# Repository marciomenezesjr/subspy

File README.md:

# subspy
Internet of Things final project

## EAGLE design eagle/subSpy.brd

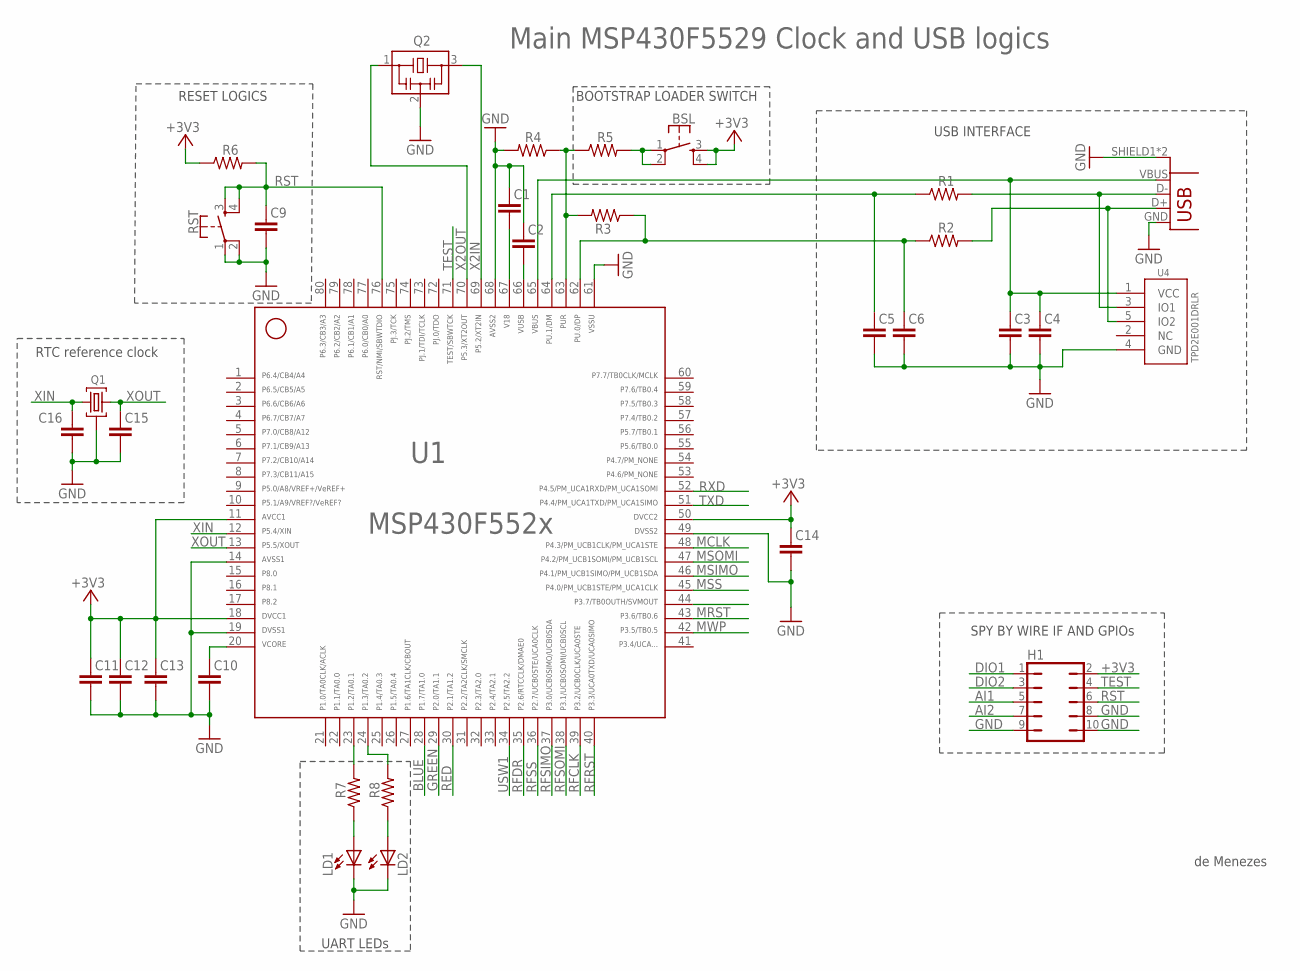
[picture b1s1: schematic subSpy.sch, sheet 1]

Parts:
BSL: DTSM-6
C1, C2: 220nF; C0402
C3: 10uF; C1206
C4, C12, C13, C14: 100nF; C0402
C5, C6: 10pF; C0603
C9: 1nF; C0603
C10: 470nF; C0603
C11: 10uF; C0805
C15, C16: 12pF; C0603
H1: JP5Q
LD1, LD2: LEDCHIP-LED0805; CHIP-LED0805
Q1: 32.768kHz; MS3V-T1R
Q2: CSTCR4M00G15L99; MURATA-FILTER_CSTCR
R1, R2: 27R; R0603
R3: 1.4k; R0603
R4: 1M; R0603
R5: 100R; R0603
R6: 47k; R0603
R7: 470R; R0603
R8: 390R; R0603
RST: DTSM-6
U1: MSP430F5529IPNR; PN80
U4: TPD2E001DRLR; TPD2E001-DRL
USB: USB_SMD; USBCONN

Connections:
+3V3: BSL.3, BSL.4, C11.1, C12.1, C13.1, C14.1, H1.2, R6.1, U1.11, U1.18, U1.50; also elsewhere on the board
AI1: H1.5
AI2: H1.7
BLUE: U1.28; also elsewhere on the board
D+: R2.2, U4.5 (IO2), USB.D+
D-: R1.2, U4.3 (IO1), USB.D-
DIO1: H1.1
DIO2: H1.3
DM: C5.1, R1.1, U1.64
DP: C6.1, R2.1, R3.1, U1.62
GND: C1.1, C2.1, C3.2, C4.2, C5.2, C6.2, C9.2, C10.2, C11.2, C12.2, C13.2, C14.2, C15.2, C16.2, H1.8, H1.9, H1.10, LD1.C, LD2.C, Q1.P3 (GND), Q2.2, R4.2, RST.1, RST.2, U1.14, U1.19, U1.49, U1.61, U1.68, U4.4 (GND), USB.GND, USB.SHIELD1 (SHIELD), USB.SHIELD2 (SHIELD); also elsewhere on the board
GREEN: U1.29; also elsewhere on the board
LD1: R7.2, U1.23
LD2: R8.2, U1.24
MCLK: U1.48; also elsewhere on the board
MRST: U1.43; also elsewhere on the board
MSIMO: U1.46; also elsewhere on the board
MSOMI: U1.47; also elsewhere on the board
MSS: U1.45; also elsewhere on the board
MWP: U1.42; also elsewhere on the board
unnamed: BSL.1, BSL.2, R5.2
unnamed: C10.1, U1.20
unnamed: LD1.A, R7.1
unnamed: LD2.A, R8.1
PUR: R3.2, R4.1, R5.1, U1.63
RED: U1.30; also elsewhere on the board
RFCLK: U1.39; also elsewhere on the board
RFDR: U1.35; also elsewhere on the board
RFRST: U1.40; also elsewhere on the board
RFSIMO: U1.37; also elsewhere on the board
RFSOMI: U1.38; also elsewhere on the board
RFSS: U1.36; also elsewhere on the board
RST: C9.1, H1.6, R6.2, RST.3, RST.4, U1.76
RXD: U1.52
TEST: H1.4, U1.71
TXD: U1.51
USW1: U1.34; also elsewhere on the board
V18: C1.2, U1.67
VBUS: C3.1, C4.1, U1.65, U4.1 (VCC), USB.VBUS; also elsewhere on the board
VUSB: C2.2, U1.66
X2IN: Q2.3, U1.69
X2OUT: Q2.1, U1.70
XIN: C16.1, Q1.P2 (2), U1.12
XOUT: C15.1, Q1.P1 (1), U1.13

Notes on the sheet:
UART LEDs
SPY BY WIRE IF AND GPIOs
USB INTERFACE
BOOTSTRAP LOADER SWITCH
RESET LOGICS
Main MSP430F5529 Clock and USB logics
RTC reference clock
de Menezes

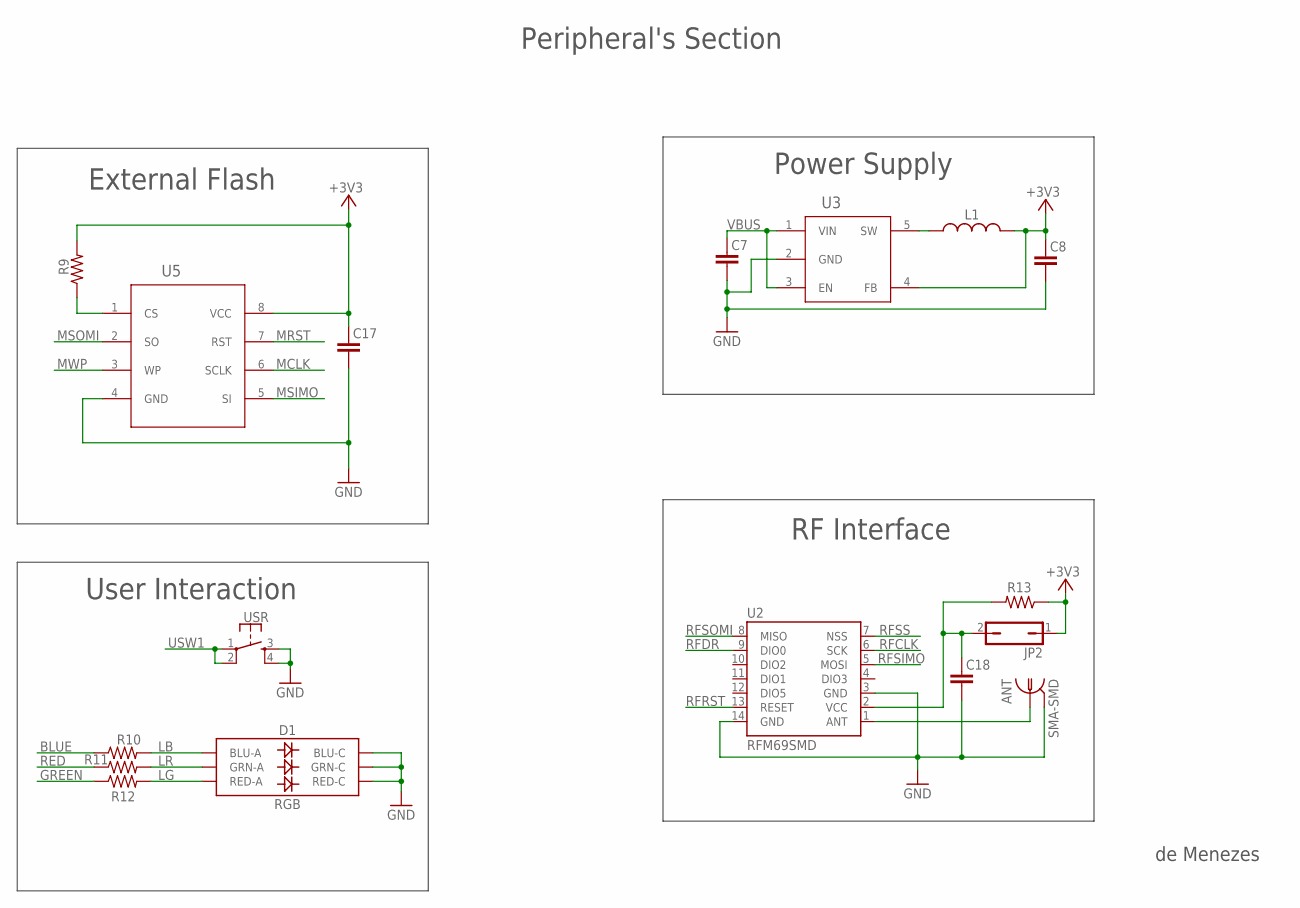
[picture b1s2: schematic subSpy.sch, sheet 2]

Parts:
ANT: SMA-SMD
C7, C8: 10uF; C0805
C17, C18: 100nF; C0402
D1: RGB; PLCC-6-LED
JP2: JP1Q; JP1
L1: INDUCTOR; L4532P
R9: 2.2k; R0603
R10, R12: ND; R0402
R11: 174R; R0402
R13: 0R; R0603
U2: RFM69SMD; RFM69
U3: Value; DBV0005A_N
U5: Value; PSA0008A_N
USR: DTSM-6

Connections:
+3V3: C8.1, C17.1, JP2.1, L1.2, R9.2, R13.1, U3.4 (FB), U5.8 (VCC); also elsewhere on the board
ANT: ANT.1, U2.1 (ANT)
BLUE: R10.1; also elsewhere on the board
GND: ANT.2@1 (2), ANT.2@2 (2), ANT.2@3 (2), ANT.2@4 (2), ANT.2@5 (2), ANT.2@6 (2), C7.2, C8.2, C17.2, C18.2, D1.CB (BLU-C), D1.CG (GRN-C), D1.CR (RED-C), U2.3 (GND), U2.14 (GND), U3.2 (GND), U5.4 (GND), USR.3, USR.4; also elsewhere on the board
GREEN: R12.1; also elsewhere on the board
LB: D1.AB (BLU-A), R10.2
LG: D1.AR (RED-A), R12.2
LR: D1.AG (GRN-A), R11.2
MCLK: U5.6 (SCLK); also elsewhere on the board
MRST: U5.7 (RST); also elsewhere on the board
MSIMO: U5.5 (SI); also elsewhere on the board
MSOMI: U5.2 (SO); also elsewhere on the board
MSS: R9.1, U5.1 (CS); also elsewhere on the board
MWP: U5.3 (WP); also elsewhere on the board
unnamed: L1.1, U3.5 (SW)
RED: R11.1; also elsewhere on the board
RFCLK: U2.6 (SCK); also elsewhere on the board
RFDR: U2.9 (DIO0); also elsewhere on the board
RFPWR: C18.1, JP2.2, R13.2, U2.2 (VCC)
RFRST: U2.13 (RESET); also elsewhere on the board
RFSIMO: U2.5 (MOSI); also elsewhere on the board
RFSOMI: U2.8 (MISO); also elsewhere on the board
RFSS: U2.7 (NSS); also elsewhere on the board
USW1: USR.1, USR.2; also elsewhere on the board
VBUS: C7.1, U3.1 (VIN), U3.3 (EN); also elsewhere on the board

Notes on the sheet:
External Flash
Power Supply
RF Interface
User Interaction
Peripheral's Section
de Menezes

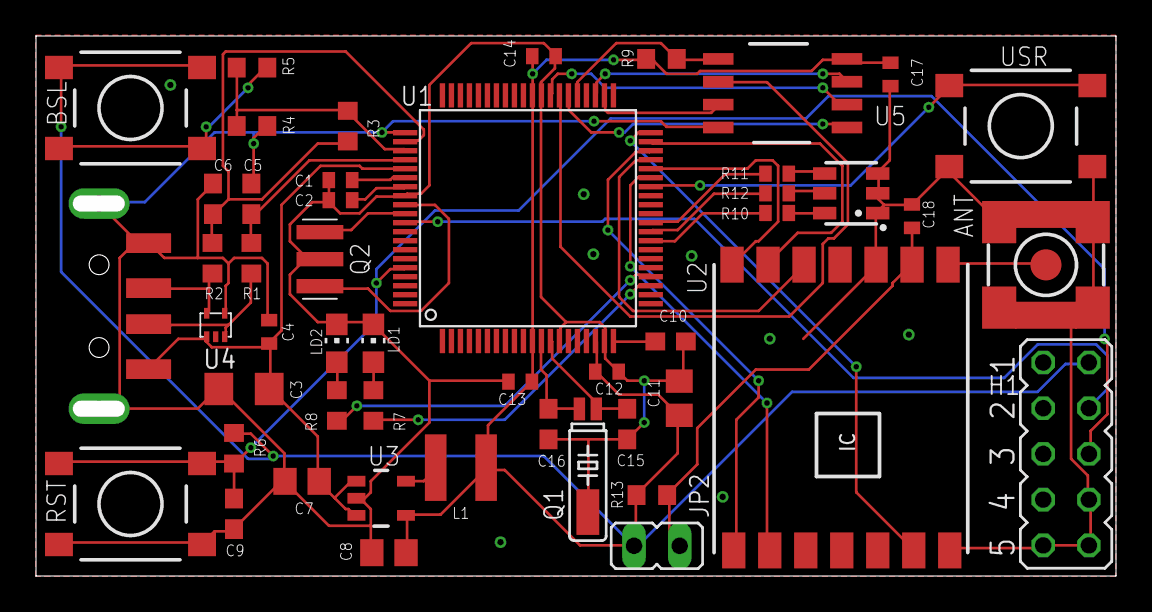
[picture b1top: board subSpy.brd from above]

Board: 2 copper layers, 60.0 x 30.0 mm, 49 parts (0 on the bottom side), 44 nets.

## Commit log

2017-06-18 Project imported from Gitlab repository

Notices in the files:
parts and their libraries:
sparkfun: Licensing: Creative Commons ShareAlike 4.0 International - https://creativecommons.org/licenses/by-sa/4.0
